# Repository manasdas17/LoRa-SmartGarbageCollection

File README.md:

LoRa-Smart Garbage Collection
=============================
 
Manas Das (manasdas17@gmail.com)

Project Description 
------------------- 
 
Deploying smart garbage bins for real time waste management system is one of the key applications of a smart city system. Municipal authorities need an efficient way to clear the trash from all public places before it becomes a mess. And this needs to be achieved with the minimum overhead of cost and impact to the city dwellers. LoRaWAN is one of the earlier LPWAN technologies that envisages a city-wide network for keeping track of public infrastructure assets. Once fitted with a BLS(Bin Level Sensing) device on a trash can, LoRaWAN allows the city authorities to keep a tab on the bins via wireless connectivity. LoRaWAN does suffer from some limitations, such as extremely low data rates, higher collision and deteriorated network performance with increasing number of nodes and inability to perform over the air updates to the device.

Technologies Used 
------------------- 
 
Remove the items that do no apply to your project and keep the remaining ones. 
 
+   Arduino/Embedded C 
+   LoRa
+   KiCad
+   Python 
+   Javascript 
+   Designed PCB with Atmega328p & Lora Module 

Installation Instructions 
========================= 
 
To run the dashboard app, please go inside the folder from terminal and type nodejs app.js 

References 
=========== 
 
Please give references to importance resources.  
 
+ [LoRa Module]http://www.microchip.com/wwwproducts/en/RN2483
+ Arduino Low-Power Library :- https://github.com/rocketscream/Low-Power
+ All other references are put in the report.

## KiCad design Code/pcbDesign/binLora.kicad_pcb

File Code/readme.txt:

LoRa-Smart Garbage Collection
========================

Manas Das (manasdas17@gmail.com)

Project Description 
------------------- 
 
Deploying smart garbage bins for real time waste management system is one of the key applications of a smart city system. Municipal authorities need an efficient way to clear the trash from all public places before it becomes a mess. And this needs to be achieved with the minimum overhead of cost and impact to the city dwellers. LoRaWAN is one of the earlier LPWAN technologies that envisages a city-wide network for keeping track of public infrastructure assets. Once fitted with a BLS(Bin Level Sensing) device on a trash can, LoRaWAN allows the city authorities to keep a tab on the bins via wireless connectivity. LoRaWAN does suffer from some limitations, such as extremely low data rates, higher collision and deteriorated network performance with increasing number of nodes and inability to perform over the air updates to the device.

Technologies Used 
------------------- 
 
Remove the items that do no apply to your project and keep the remaining ones. 
 
+   Arduino/Embedded C 
+   LoRa
+   KiCad
+   Python 
+   Javascript 
+   Designed PCB with Atmega328p & Lora Module 

Installation Instructions 
========================= 
 
To run the dashboard app, please go inside the folder from terminal and type nodejs app.js 

References 
=========== 
 
Please give references to importance resources.  
 
+ [LoRa Module]http://www.microchip.com/wwwproducts/en/RN2483
+ All other references are put in the report.

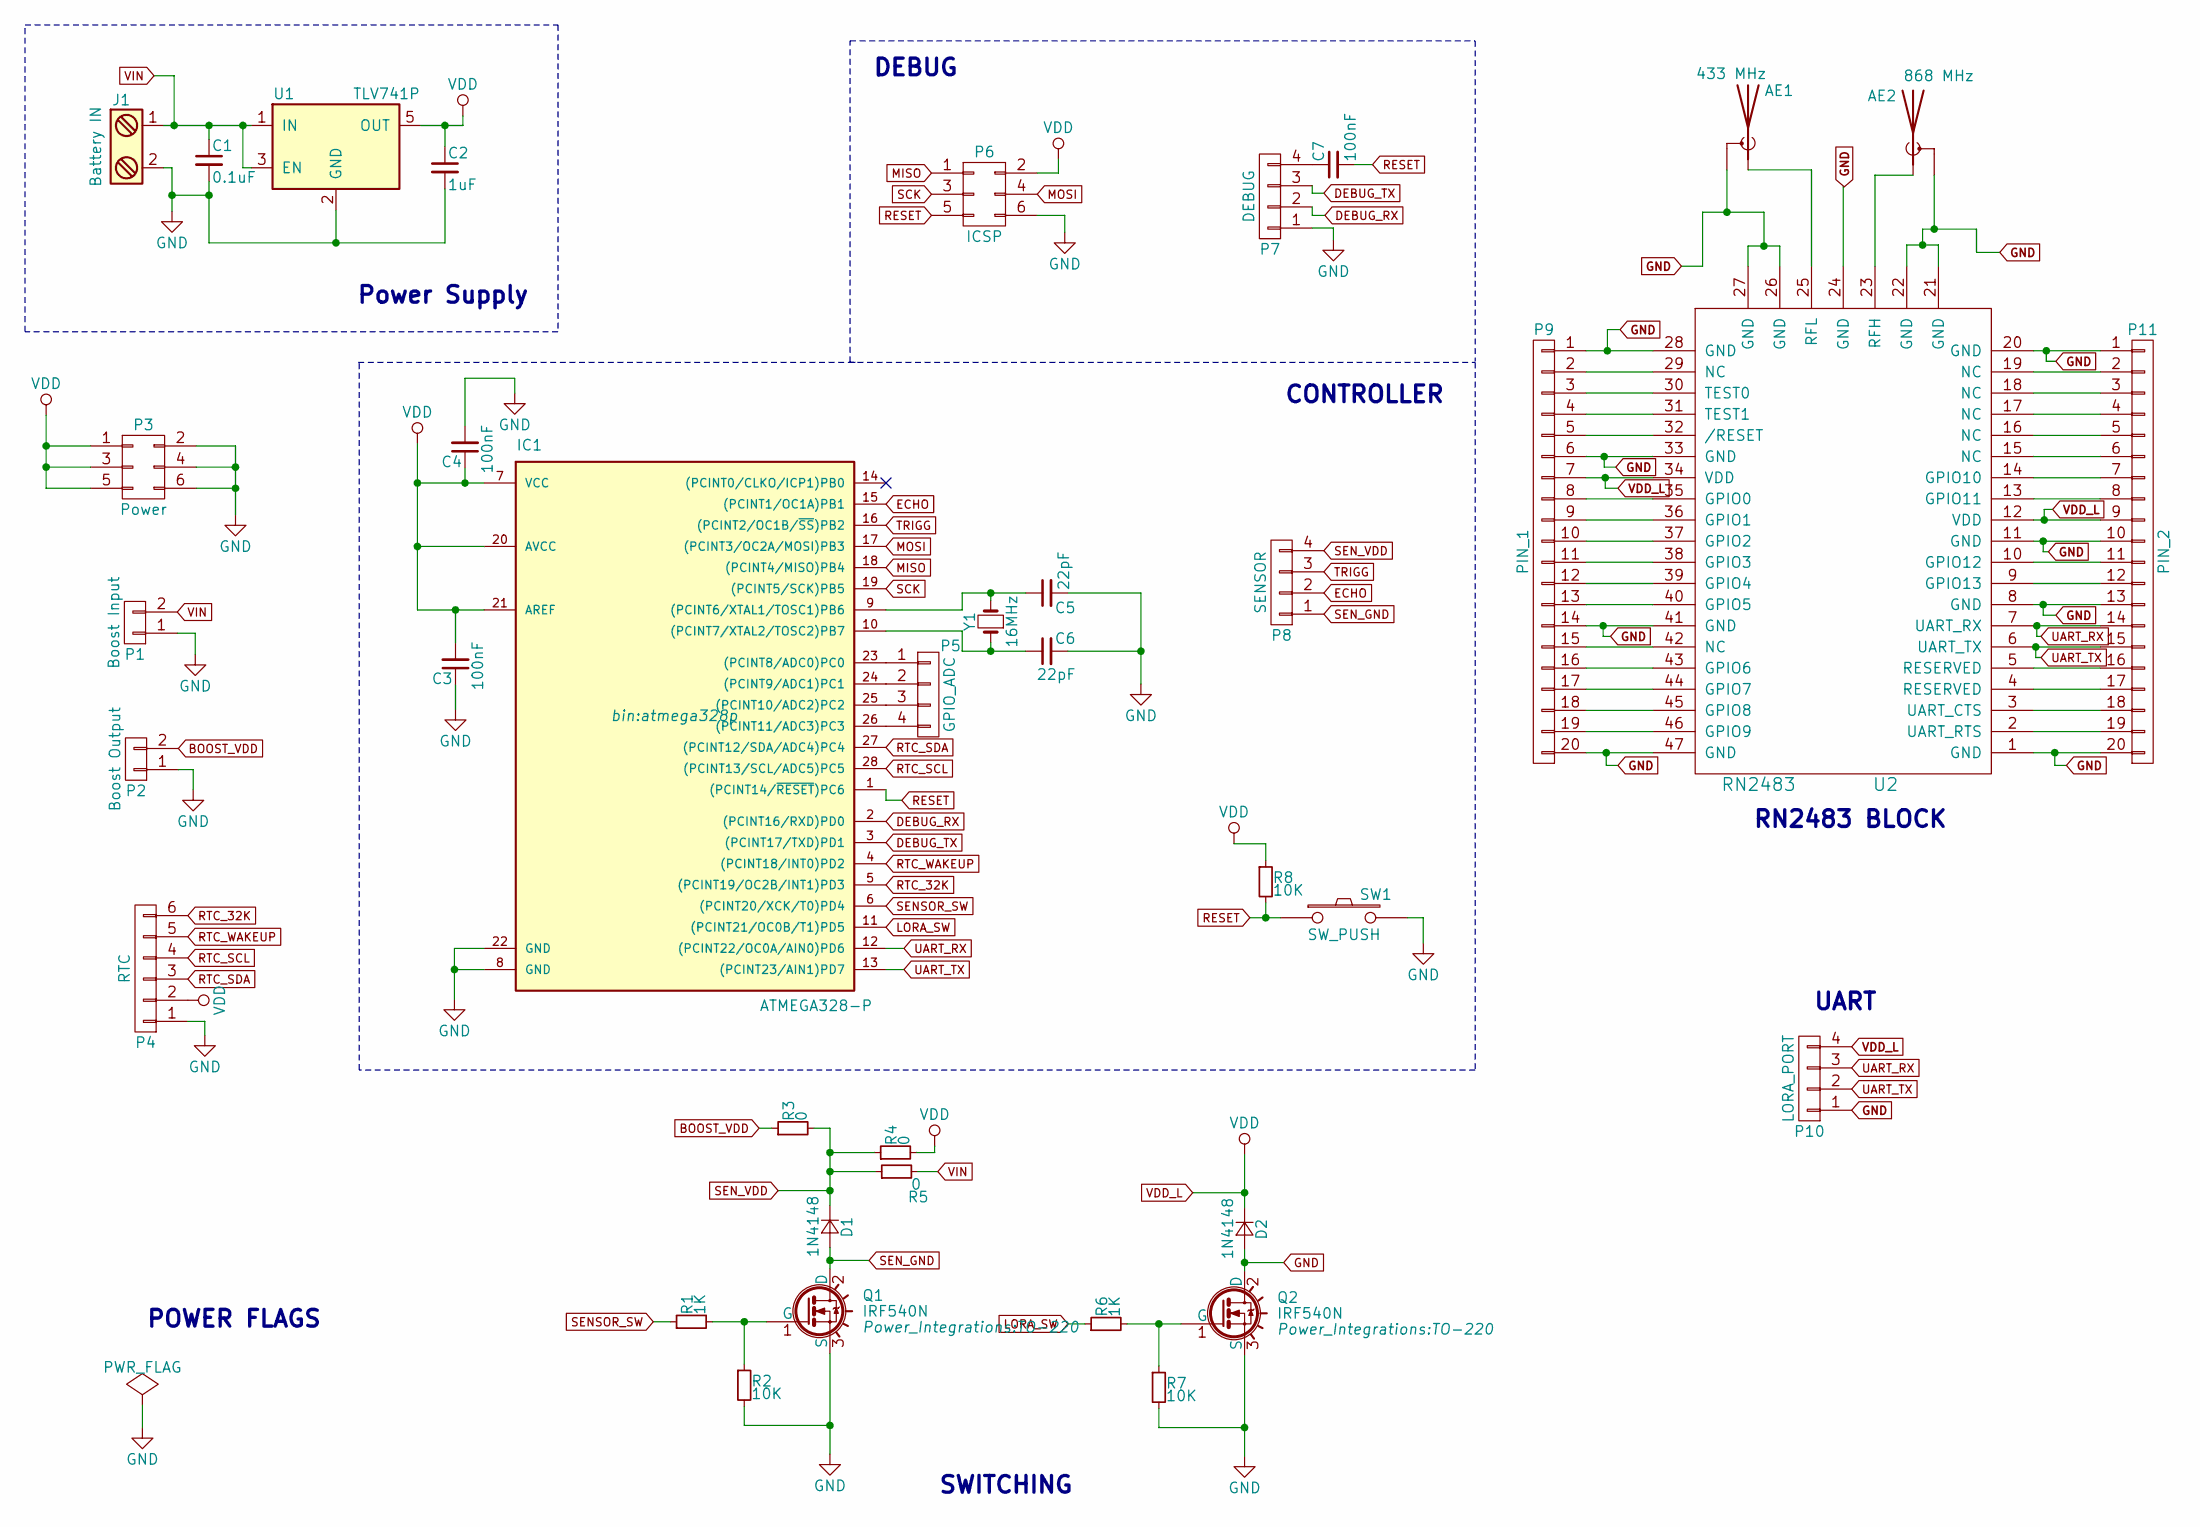
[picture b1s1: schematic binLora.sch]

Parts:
AE1: 433 MHz; SMA_THT_Jack_Straight
AE2: 868 MHz; SMA_THT_Jack_Straight
C1: 0.1uF; C_Disc_D3.0mm_W1.6mm_P2.50mm
C2: 1uF; C_Disc_D4.3mm_W1.9mm_P5.00mm
C3, C4, C7: 100nF; C_Disc_D4.7mm_W2.5mm_P5.00mm
C5, C6: 22pF; C_Disc_D3.0mm_W1.6mm_P2.50mm
D1, D2: 1N4148; D_5W_P12.70mm_Horizontal
IC1: ATMEGA328-P; atmega328p
J1: Battery IN; TerminalBlock_bornier-2_P5.08mm
P1: Boost Input; Pin_Header_Straight_1x02_Pitch2.54mm
P2: Boost Output; Pin_Header_Straight_1x02_Pitch2.54mm
P3: Power; Pin_Header_Straight_2x03_Pitch2.54mm
P4: RTC; Pin_Header_Straight_1x06_Pitch2.54mm
P5: GPIO_ADC; Pin_Header_Straight_1x04_Pitch2.54mm
P6: ICSP; Pin_Header_Straight_2x03_Pitch2.54mm
P7: DEBUG; Pin_Header_Straight_1x04_Pitch2.54mm
P8: SENSOR; Pin_Header_Straight_1x04_Pitch2.54mm
P9: PIN_1; Pin_Header_Straight_1x20_Pitch2.54mm
P10: LORA_PORT; Pin_Header_Straight_1x04_Pitch2.54mm
P11: PIN_2; Pin_Header_Straight_1x20_Pitch2.54mm
Q1, Q2: IRF540N; TO-220
R1, R6: 1K; R_Axial_DIN0207_L6.3mm_D2.5mm_P7.62mm_Horizontal
R2, R7, R8: 10K; R_Axial_DIN0207_L6.3mm_D2.5mm_P7.62mm_Horizontal
R3, R4, R5: 0; R_Axial_DIN0207_L6.3mm_D2.5mm_P7.62mm_Horizontal
SW1: SW_PUSH; SW_PUSH_6mm
U1: TLV741P; SOT-23-5
U2: RN2483
Y1: 16MHz; Crystal_HC49-U_Vertical

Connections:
BOOST_VDD: P2.2, R3.1
DEBUG_RX: IC1.2 ((PCINT16/RXD)PD0), P7.2
DEBUG_TX: IC1.3 ((PCINT17/TXD)PD1), P7.3
ECHO: IC1.15 ((PCINT1/OC1A)PB1), P8.2
GND: AE1.2 (Shield), AE2.2 (Shield), C1.2, C2.2, C3.1, C4.2, C5.2, C6.2, D2.2 (A), IC1.8 (GND), IC1.22 (GND), J1.2, P1.1, P2.1, P3.2, P3.4, P3.6, P4.1, P6.6, P7.1, P9.1, P9.6, P9.14, P9.20, P10.1, P11.1, P11.10, P11.13, P11.20, Q1.3 (S), Q2.2 (D), Q2.3 (S), R2.2, R7.2, SW1.2, U1.2 (GND), U2.1 (GND), U2.8 (GND), U2.11 (GND), U2.20 (GND), U2.21 (GND), U2.22 (GND), U2.24 (GND), U2.26 (GND), U2.27 (GND), U2.28 (GND), U2.33 (GND), U2.41 (GND), U2.47 (GND)
LORA_SW: IC1.11 ((PCINT21/OC0B/T1)PD5), R6.1
MISO: IC1.18 ((PCINT4/MISO)PB4), P6.1
MOSI: IC1.17 ((PCINT3/OC2A/MOSI)PB3), P6.4
unnamed: AE1.1 (A), U2.25 (RFL)
unnamed: AE2.1 (A), U2.23 (RFH)
unnamed: C5.1, IC1.9 ((PCINT6/XTAL1/TOSC1)PB6), Y1.2
unnamed: C6.1, IC1.10 ((PCINT7/XTAL2/TOSC2)PB7), Y1.1
unnamed: C7.1, P7.4
unnamed: IC1.23 ((PCINT8/ADC0)PC0), P5.1
unnamed: IC1.24 ((PCINT9/ADC1)PC1), P5.2
unnamed: IC1.25 ((PCINT10/ADC2)PC2), P5.3
unnamed: IC1.26 ((PCINT11/ADC3)PC3), P5.4
unnamed: P9.2, U2.29 (NC)
unnamed: P9.3, U2.30 (TEST0)
unnamed: P9.4, U2.31 (TEST1)
unnamed: P9.5, U2.32 (/RESET)
unnamed: P9.8, U2.35 (GPIO0)
unnamed: P9.9, U2.36 (GPIO1)
unnamed: P9.10, U2.37 (GPIO2)
unnamed: P9.11, U2.38 (GPIO3)
unnamed: P9.12, U2.39 (GPIO4)
unnamed: P9.13, U2.40 (GPIO5)
unnamed: P9.15, U2.42 (NC)
unnamed: P9.16, U2.43 (GPIO6)
unnamed: P9.17, U2.44 (GPIO7)
unnamed: P9.18, U2.45 (GPIO8)
unnamed: P9.19, U2.46 (GPIO9)
unnamed: P11.2, U2.19 (NC)
unnamed: P11.3, U2.18 (NC)
unnamed: P11.4, U2.17 (NC)
unnamed: P11.5, U2.16 (NC)
unnamed: P11.6, U2.15 (NC)
unnamed: P11.7, U2.14 (GPIO10)
unnamed: P11.8, U2.13 (GPIO11)
unnamed: P11.11, U2.10 (GPIO12)
unnamed: P11.12, U2.9 (GPIO13)
unnamed: P11.16, U2.5 (RESERVED)
unnamed: P11.17, U2.4 (RESERVED)
unnamed: P11.18, U2.3 (UART_CTS)
unnamed: P11.19, U2.2 (UART_RTS)
unnamed: Q1.1 (G), R1.2, R2.1
unnamed: Q2.1 (G), R6.2, R7.1
RESET: C7.2, IC1.1 ((PCINT14/~RESET~)PC6), P6.5, R8.2, SW1.1
RTC_32K: IC1.5 ((PCINT19/OC2B/INT1)PD3), P4.6
RTC_SCL: IC1.28 ((PCINT13/SCL/ADC5)PC5), P4.4
RTC_SDA: IC1.27 ((PCINT12/SDA/ADC4)PC4), P4.3
RTC_WAKEUP: IC1.4 ((PCINT18/INT0)PD2), P4.5
SCK: IC1.19 ((PCINT5/SCK)PB5), P6.3
SENSOR_SW: IC1.6 ((PCINT20/XCK/T0)PD4), R1.1
SEN_GND: D1.2 (A), P8.1, Q1.2 (D)
SEN_VDD: D1.1 (K), P8.4, R3.2, R4.1, R5.1
TRIGG: IC1.16 ((PCINT2/OC1B/~SS~)PB2), P8.3
UART_RX: IC1.12 ((PCINT22/OC0A/AIN0)PD6), P10.3, P11.14, U2.7 (UART_RX)
UART_TX: IC1.13 ((PCINT23/AIN1)PD7), P10.2, P11.15, U2.6 (UART_TX)
VDD_L: C2.1, C3.2, C4.1, D2.1 (K), IC1.7 (VCC), IC1.20 (AVCC), IC1.21 (AREF), P3.1, P3.3, P3.5, P4.2, P6.2, P9.7, P10.4, P11.9, R4.2, R8.1, U1.5 (OUT), U2.12 (VDD), U2.34 (VDD)
VIN: C1.1, J1.1, P1.2, R5.2, U1.1 (IN), U1.3 (EN)

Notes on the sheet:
RN2483 BLOCK
UART
Power Supply
DEBUG
CONTROLLER
SWITCHING
POWER FLAGS

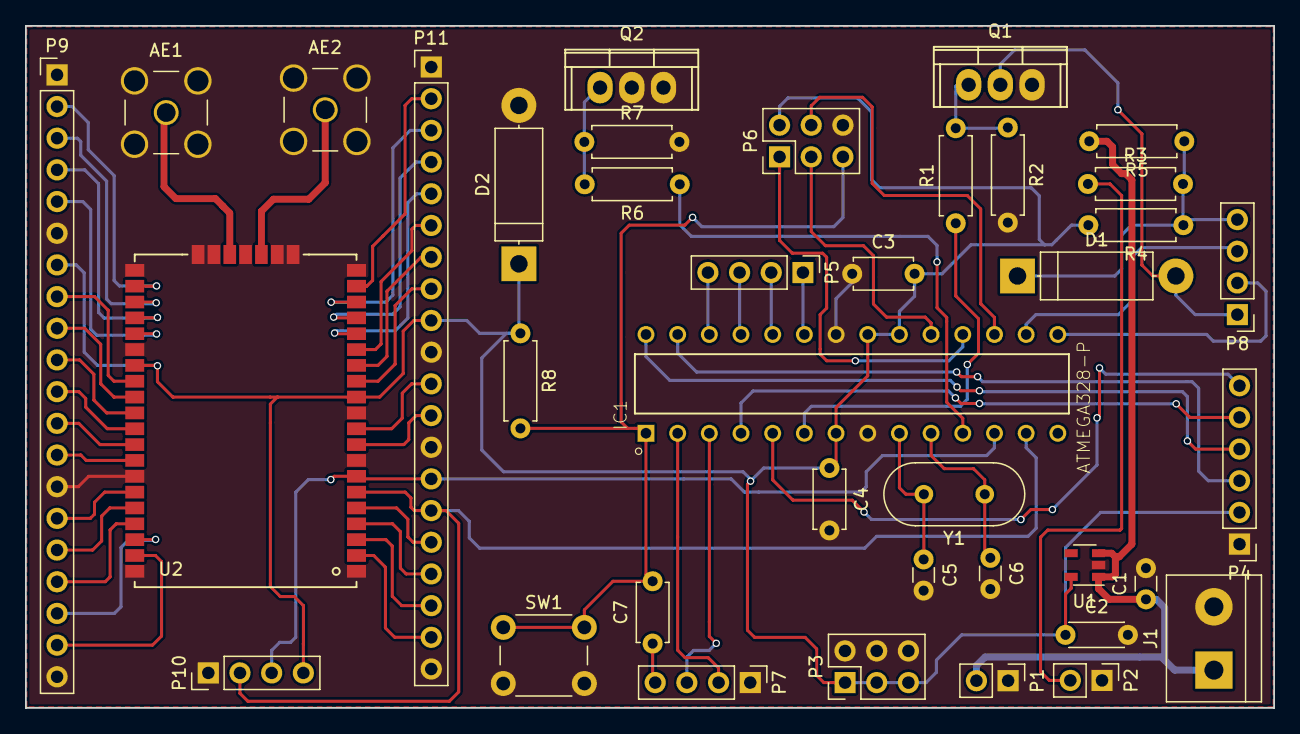
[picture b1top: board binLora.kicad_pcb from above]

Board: 2 copper layers, 100.1 x 54.7 mm, 38 parts (0 on the bottom side), 61 nets.

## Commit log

2018-05-28 Add final submission with Arduno Library Low Power
